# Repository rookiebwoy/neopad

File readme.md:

# Neopad

## Overview

Neopad is a little macropad with four switches and two rotary encoders, made by through hole components only. It's designed to use [QMK](https://qmk.fm/) firmware.
_Actually the number of switches is six, because even the encoder are allowed to click._

The Neopad in the photo above is the first prototype with ultra light case made from biscuits cardboard. In this repo you can find the final revision including:

+ fixed reset button pin routing
+ fixed positioning of mounting holes
+ added breakable PCB for EOTW case
+ new shiny artwork

Read the full development log on my website: [rookiebwoy.eu](https://www.rookiebwoy.eu/projects/neopad/neopad.html).

## In this repo

Here you can find my KiCad project files and the gerbers I used to manufacture the Neopad.
In order to open and modify them you will need to download and add the [keebio-components](https://github.com/keebio/keebio-components.git) symbols library to the project's path.

PCB's frontside.

PCB's backside.

## Description

+ The 2 LEDs rappresent the current layer in binary (max 4 layers rappresented but, accordingly with [QMK capabilities](https://beta.docs.qmk.fm/using-qmk/software-features/feature_layers), you can program up to 16 layers)
+ Total PCB dimensions are 99.22mm x 87.31mm
+ Macropad dimensions after build are 99.22mm x 42.86mm

## BOM

|Qty    |Description                            |
|------:|:--------------------------------------|
|1x 	|Pro-Micro (or clone with ATmega32u4)   |
|4x 	|Cherry MX compatible switches          |
|2x 	|Encoders EC11                          |
|6x     |Diodes THT do-35 1N4148                |
|2x 	|Resistors 1/4W 220ohm         	        |
|2x 	|LEDs 3mm                      	        |
|1x 	|Button switch 4 pin 6mm x 6mm	        |
|4x 	|M2 8mm standoff               	        |
|8x 	|M2 screws                     	        |
|6x 	|Rubber feet                 	        |
|4x 	|Keycaps                     	        |
|2x 	|Knobs                       	        |

## Firmware

You can find the QMK Firmware for Neopad on the official QMK repository at [this link](https://github.com/qmk/qmk_firmware/tree/master/keyboards/neopad).

## References

I decided to open source this project because I wanted to give back to the amazing mechanical keyboard comunity what was given to me. I owe special mention to the following links that I found extremely useful and that without them I could never achieve this:

+ the keyboard designer wiki [@ ai03.com](https://wiki.ai03.com/books/pcb-design/chapter/pcb-designer-guide) for KiCad's tutorial
+ Chokkan's [YouTube videos](https://www.youtube.com/watch?v=-HLV6mUxNnU) for setting up QMK's developing environment
+ imchipwood's [dumbpad macropad](https://github.com/imchipwood/dumbpad) for encoder's routing, LED's behavior, QMK and readme structure

## Donations

If you've found something useful, please consider helping me maintain [my website](https://www.rookiebwoy.eu/) online and further develop all my projects.

<p align="center">

</p>

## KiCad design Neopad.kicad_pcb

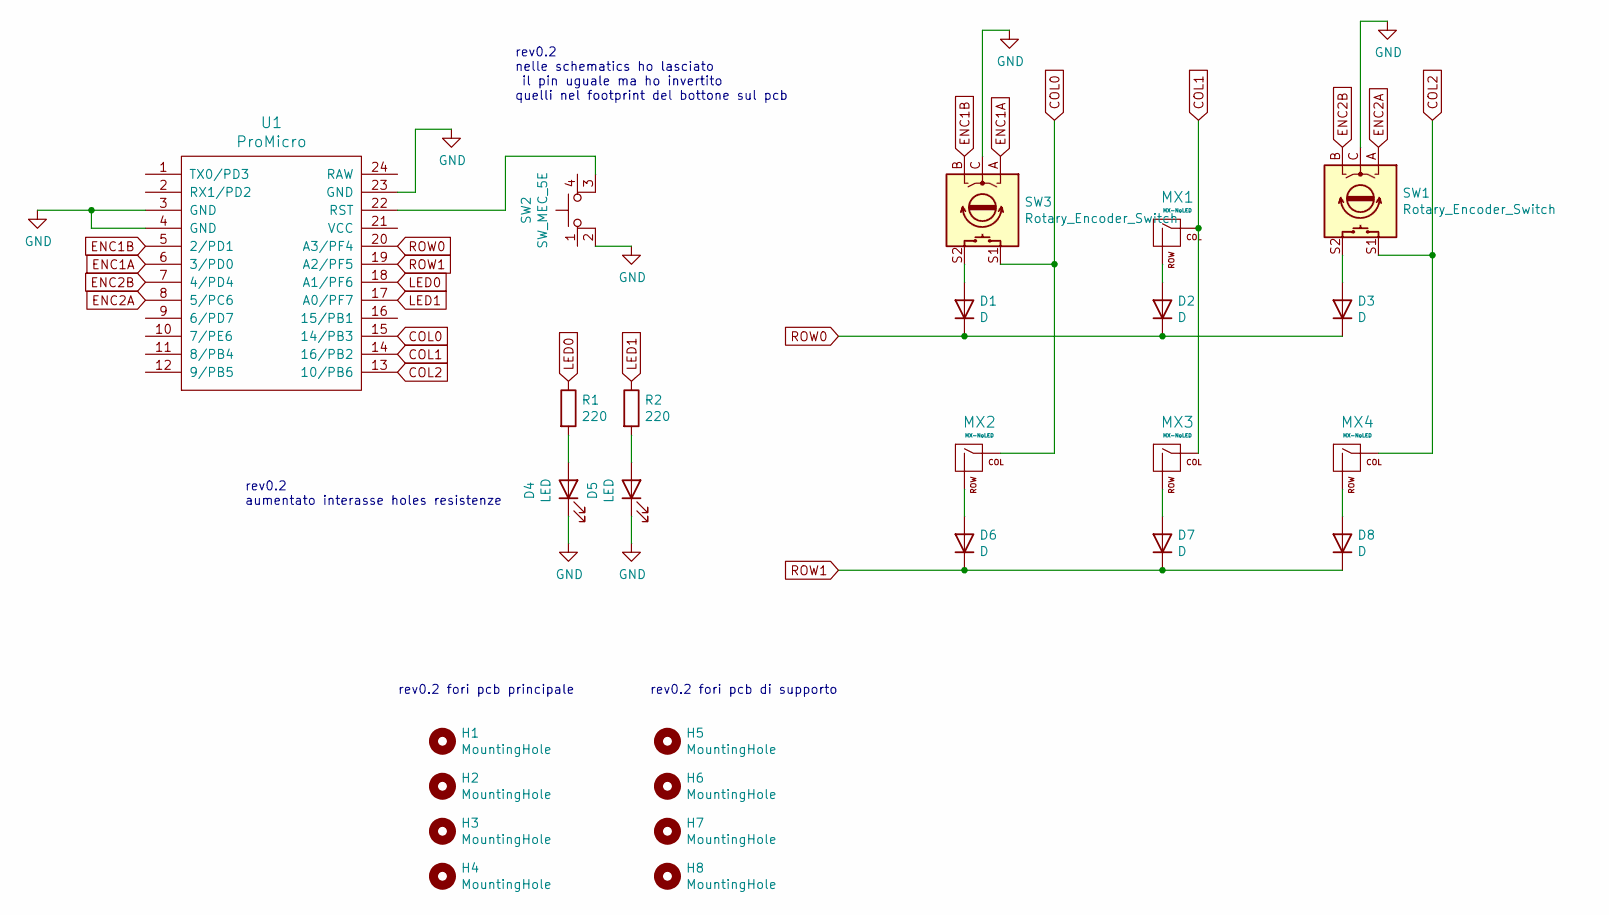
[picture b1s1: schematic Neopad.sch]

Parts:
D1, D2, D3, D6, D7, D8: D; Diode_DO-35_SOD27_P7.62mm
D4, D5: LED; LED_D3.0mm
H1, H2, H3, H4, H5, H6, H7, H8: MountingHole; MountingHole_D2.3mm
MX1, MX2, MX3, MX4: MX-NoLED; MXOnly-1U-NoLED
R1, R2: 220; R_Axial_P7.62mm
SW1, SW3: Rotary_Encoder_Switch; RotaryEncoder_Alps_EC11E-Switch
SW2: SW_MEC_5E; Button_SW_6mm
U1: ProMicro; ArduinoProMicro

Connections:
COL0: MX2.1 (COL), SW3.S1, U1.15 (14/PB3)
COL1: MX1.1 (COL), MX3.1 (COL), U1.14 (16/PB2)
COL2: MX4.1 (COL), SW1.S1, U1.13 (10/PB6)
ENC1A: SW3.A, U1.6 (3/PD0)
ENC1B: SW3.B, U1.5 (2/PD1)
ENC2A: SW1.A, U1.8 (5/PC6)
ENC2B: SW1.B, U1.7 (4/PD4)
GND: D4.1 (K), D5.1 (K), SW1.C, SW2.2, SW3.C, U1.3 (GND), U1.4 (GND), U1.23 (GND)
LED0: R1.1, U1.18 (A1/PF6)
LED1: R2.1, U1.17 (A0/PF7)
unnamed: D1.2 (A), SW3.S2
unnamed: D2.2 (A), MX1.2 (ROW)
unnamed: D3.2 (A), SW1.S2
unnamed: D4.2 (A), R1.2
unnamed: D5.2 (A), R2.2
unnamed: D6.2 (A), MX2.2 (ROW)
unnamed: D7.2 (A), MX3.2 (ROW)
unnamed: D8.2 (A), MX4.2 (ROW)
unnamed: SW2.3 (K), U1.22 (RST)
ROW0: D1.1 (K), D2.1 (K), D3.1 (K), U1.20 (A3/PF4)
ROW1: D6.1 (K), D7.1 (K), D8.1 (K), U1.19 (A2/PF5)

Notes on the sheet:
rev0.2 nelle schematics ho lasciato il pin uguale ma ho invertito quelli nel footprint del bottone sul pcb
rev0.2 aumentato interasse holes resistenze
rev0.2 fori pcb principale
rev0.2 fori pcb di supporto

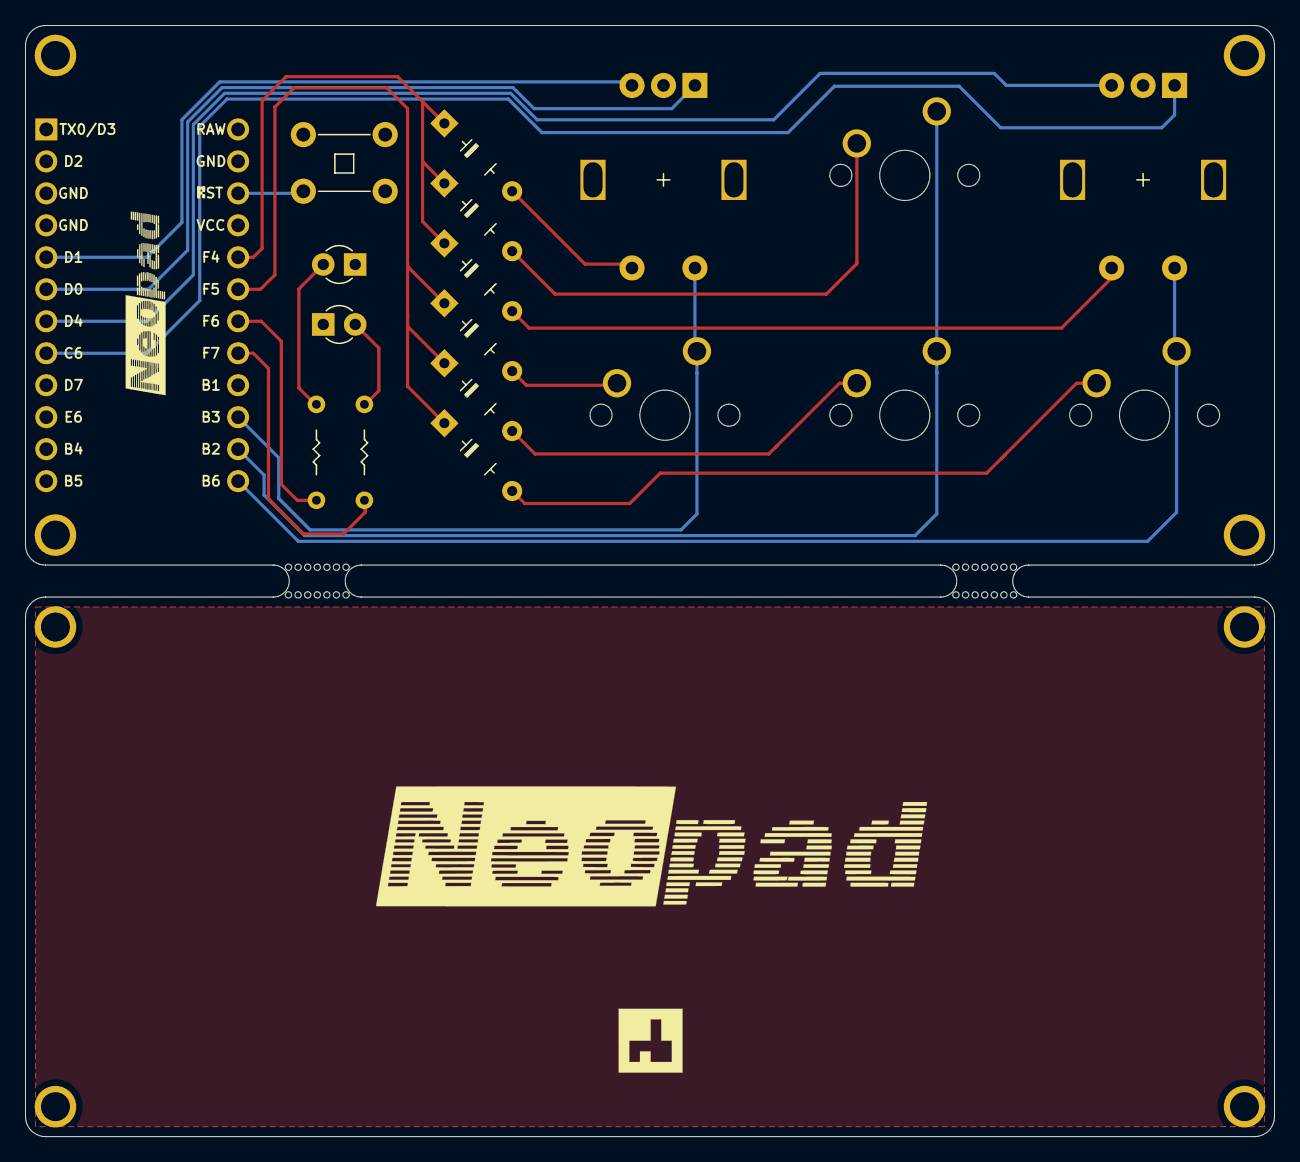
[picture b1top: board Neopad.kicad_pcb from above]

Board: 2 copper layers, 99.2 x 88.3 mm, 28 parts (0 on the bottom side), 21 nets.

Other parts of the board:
mouse-bite-2.54mm-slot, mouse-bite-2.54mm-slot#2: VAL**; MouseBite-H2.54mm-W4.57mm

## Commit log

2021-04-18 creazione repository
2021-04-18 aggiunti file progetto
2021-04-18 aggiunto file readme
2021-04-18 Added license
2021-04-18 aggiornato readme
2021-04-19 aggiunti ringraziamenti
2021-05-15 Aggiunto paragrafo firmware
2021-06-16 PCB revision for manufacturing improvement
2022-03-06 added donation section
2022-03-06 added website link
